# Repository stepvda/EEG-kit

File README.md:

# EEG Field Kit — Design & Production Package v2.4

**TI One Voice research programme** — [one.witysk.org](https://one.witysk.org), Brussels, Belgium
Board revision B · 2 September 2026

The complete manufacturing package for **EEG-CAR-01 Rev B**: a battery-powered, 16-channel EEG headset
built around an ESP32-S3 carrier board, together with the helmet and enclosure, the electrode harness,
the firmware, the production test programme and fixtures, and all the packing, quality and regulatory
documentation needed to produce the finished kit — flight case included.

The package is designed so that a manufacturer can quote, review and build from it directly: the
Gerbers, drill files, netlist, BOM and CPL files are included, along with every printed part, the
assembly work instructions and an end-to-end test programme that runs from Chrome over USB. For the
study itself — participants, collaborators, grant bodies and funders — see
[one.witysk.org/studies](https://one.witysk.org/studies).

---

## Status at a glance

**Nothing in this package has been manufactured or measured.** No board has been fabricated, no part
has been printed, no firmware has been flashed to silicon, and no electrode has touched a person.
Every performance figure is calculated, and each is labelled as calculated where it appears.

| Area | State |
|---|---|
| Carrier board routing | **Complete.** 145 of 145 nets connected, 0 DRC violations. **Released for review under RFQ-EEG-002A — not yet released for fabrication:** no human layout engineer has reviewed it, and 169 connections close at relaxed width or gap. |
| Firmware | **Built and boots under QEMU** (ESP-IDF v5.2.5, esp32s3). Never run on real hardware — no hardware exists. |
| Mechanical parts | 29 STL + 28 STEP released. Nothing has been printed. Foam case insert **not released for cutting** until the helmet shell is measured. |
| Test programme | Written and self-tested (57/57 interop checks). Never run against a physical unit. |
| Production simulation | 193 checks passed, 0 failed, 6 open items. |
| Safety | **Not done.** The safety review gates Phase 2; nothing goes on a head before it. |

**Read [`KNOWN_ISSUES.txt`](KNOWN_ISSUES.txt) before quoting or building anything.** It is the short
list, in one place, of what is wrong with the data as shipped — 6 open items and 22 unapproved
assumptions in 15 sections. Everything in it is also in the controlled documents; the file exists so
that problems are found here rather than at CAM time.

---

## Orientation — read in this order

1. **`README_package_index.txt` + `KNOWN_ISSUES.txt`** — the orientation pair. The index says what
   every folder is for and gives the rebuild commands (its header is stale at v2.2; this package
   is v2.4).
2. **`docs/RFQ-EEG-001 Rev E`** — the actual request: numbered requirements (E-, S-, F-, T-), the
   pricing template, and §9.4's correction-iteration terms for prototypes that arrive not working.
3. **`docs/DSN-EEG-003 Rev D`** — the governing document. Architecture, the carrier board, and the
   precedence rules that decide which document wins when two disagree.

**Precedence:** DSN-EEG-003 Rev D > RFQ-EEG-001 Rev E > ICD-EEG-006 > SCH-EEG-005 > DSN-EEG-002 >
PARTS-EEG-019 > RUL-EEG-021 > the bidder BOM. Where a number appears in a document *and* in
`tools/design.py`, **design.py governs** — `tools/emit_all.py` regenerates every fabrication file
from it in one pass, so the package cannot drift.

---

## Repository layout

| Path | Contents |
|---|---|
| `docs/` | 21 controlled documents (Rev-controlled, in `.md`, `.docx` and `.pdf`): the RFQ, the manufacturing design package, interface control, schematic set, assembly work instructions, harness wire list, test specification, fixture design, quality plan, risk & safety pack, regulatory file (incl. lithium shipping UN3481/PI967), service & refurbishment, participant card, packing & labelling, change control, approved vendor list, production simulation, part register, firmware build & provisioning, rulings register — plus the three workbooks: bidder BOM, internal costed BOM, manufacturer contacts. |
| `kicad/` | **EEG-CAR-01 Rev B fabrication pack:** routed `.kicad_pcb`, DRC report, BOM, two CPL files, fabrication/assembly/copper drawings, PCB spec sheet, machine-readable net report — and `gerber/`: 11 Gerber X2 layers, two Excellon drills, IPC-D-356A netlist, zipped, with a SHA-256 for every file. |
| `kicad/wh-bus-01/` | The second, tiny PCB: 14 × 10 × 0.8 mm bus board that splits the harness LED_V into eight contact-light tails. The helmet doesn't work without it. |
| `schematic/` | SCH-EEG-005 Rev B, an 8-sheet A3 schematic set (PDF + PNGs), generated from `tools/design.py`. Drawings only — there is no editable `.kicad_sch`. |
| `mech/` | Every printed and cut part: `stl/` (29 printable meshes), `step/` (28 parametric solids for dimensioning and inspection), `drawings/` (25 dimensioned sheets), `renders/` (25 shaded views), 7 foam-layer DXFs for the flight case, the hardware schedule and the mechanical release status. |
| `firmware/` | The ESP-IDF project (main.c, drivers, provisioning opcodes) and `release/`: four flashable ESP32-S3 images (bootloader, partition table, OTA data, app) with a SHA-256 manifest and the exact `esptool` command — no toolchain needed to program a board. `firmware/tools/` is the end-of-line provisioning station: ATECC608B keying, serial & calibration writes, signed-stream verification. |
| `webtest/` | **TOOL-EEG-022**, the connectivity test: one self-contained 52 kB HTML file an assembler double-clicks in Chrome to prove browser–computer–USB–device connectivity (no measurement, no server, nothing to install). The interop harness compiles the real `main.c` against ESP-IDF stubs and drives it with the real host protocol module — 57/57 checks green. |
| `fixtures/` | The four production test fixtures of JIG-EEG-009 as buildable data: PCB outlines and netlists (deliberately no copper), printed-part geometry, and RP2040 controller firmware speaking the FIXPROTO v1 line protocol. Nothing here has been built. |
| `records/` | The machine-readable per-unit test record of TST-EEG-004 §12: a JSON Schema, a stdlib-only validator, and a worked example (all-DEFERRED). No unit has been built, so the schema has never met real output. |
| `graphics/` | Board plots (four copper layers, fabrication drawing, drill map, assembly views, 3D renders) and `labels/`: the packing and marking artwork of PKG-EEG-015 — unit label, kit ID plate, 9 foam bay tags, carton set, lithium mark, tamper seal, disinfection card (22 SVG + 11 PDF). |
| `tools/` | The generator: 42 Python modules, 19,072 lines, 27 entry points. `design.py` is the single source of truth for the board; `mech_gen.py` for the printed parts. Five re-runnable verification gates check connectivity, DRC, placement, cross-document consistency and the 15-station production dry run. Every figure in this package can be regenerated from source. |
| `project/` | Why the kit exists: the 3-page partner proposal, the 161-page experiment design v4.2, and the 11-page project plan with its schedule and workstreams (supplier costs are placeholders). |
| `reports/` | Working DRC reports, metrics and the placement checklist from the routing campaign. |
| `constraints/` | Net rules used by the router. |

---

## The board

**EEG-CAR-01 Rev B** — 150.0 × 130.0 mm, four layers (L1 signal, L2/L3 reference planes split
AGND_REF/DGND, L4 signal), 30 connectors, 211 reference designators, 156 nets.

- 3,745 track segments, 552 through vias, 0 duplicates
- 145 of 145 nets one connected copper island; **0 DRC violations**
- Smallest clearance 0.260 mm, narrowest conductor 0.200 mm, smallest plated hole 0.300 mm
- No digital net in the analogue zone; exactly one AGND_REF-to-DGND bridge and one
  HARN_SHIELD-to-DGND bridge

The layout was produced by the programme's own constraint-aware autorouter and verified by
measurement on the finished polygons — but it has **not** been reviewed by a human layout
engineer. The DRC report lists every one of the 169 relaxed connections so a reviewer can go
straight to the places that need attention.

## Firmware

ESP-IDF v5.2.5, target esp32s3, Phase 1 configuration (secure boot off). Four release images with
SHA-256 checksums, a 920-line `main.c` with 16 host commands and 13 provisioning opcodes, drivers
for the ES8388 codec, SDMMC, ATECC608B, MAX17048 gauge and the envelope onset detector.

| What has happened | What it proves | What it does not |
|---|---|---|
| It builds, clean at `-Wall -Werror=all` | The image links and fits | That any of it is right |
| It boots under QEMU (esp32s3) | Bootloader, partition table and `app_main()` behave as written | Any peripheral — QEMU has no PSRAM, SD, ES8388 or ADS1299 |
| It agrees with the browser tool (57/57) | Framing, CRC, opcodes, the S-01 interlock | Anything about ESP-IDF or hardware |

**It has never run on silicon, and no hardware exists.** The SPI timing, every ADS1299 register
value, USB enumeration and the whole analogue front end are assumptions no silicon has answered.
F-08 (block signing) is unimplemented; the ATECC608B config template is only 4 of 128 bytes
reviewed — that write is irreversible, so it gates on a real part.

## Testing & quality

- **TST-EEG-004 Rev C** — the per-unit test: 32 steps T00–T30, with a 5,033-line JSON Schema and a
  stdlib-only validator so any two vendors emit the same record file.
- **JIG-EEG-009 Rev C + `fixtures/`** — four test fixtures as buildable data, with RP2040
  controller firmware passing 154 host checks.
- **TOOL-EEG-022** — the browser connectivity test (`webtest/EEG-Connectivity-Test.html`) and the
  interop harness that keeps firmware and protocol from drifting apart.
- **SIM-EEG-018** — a production simulation that walks one unit through all fifteen stations,
  purchase order to refurbishment: **193 passed, 0 failed, 6 open**.
- **ECO-EEG-016** — the change register that owns the document namespace and explains why
  everything is the way it is.

## Rebuilding the package from source

```sh
python3 tools/run_build.py          # route, pour, check            (~20 min)
python3 tools/emit_all.py --cached  # Gerbers, drawings, schematic
python3 tools/emit_extras.py        # spec sheet, netreport, STEP, manifest
python3 tools/mech_gen.py           # STL and STEP for every printed part
python3 tools/mech_drawings.py      # dimensioned drawings and renders
python3 tools/emit_workbooks.py     # the three spreadsheets
python3 tools/simulate_production.py --report docs/SIM-EEG-018_....md
python3 tools/make_docs.py          # A4 .docx and .pdf of every document

python3 tools/check_consistency.py  # cross-document consistency gate
python3 webtest/build.py            # rebuild the single-file connectivity tester
node webtest/tests/*.mjs            # protocol tests
sh webtest/tests/interop/run.sh     # firmware-vs-protocol interop (57 checks)
```

## Production phases

1. **Phase 1** — 2 prototypes
2. **Phase 2** — 10 kits
3. **Phase 3** — 10 to 40 further kits (25 to 50 total)

## Sponsorship

This study is run by a non-profit and funded by donations and grants that have not yet all been
secured. Any part of the work treated as sponsorship — a discounted prototype build, parts at
cost, donated units — is welcome, in return for named credit in the published open-hardware design
files, acknowledgement in the resulting papers and on the platform, and the case study of an
instrument you built being used in a pre-registered study.

## Licence & contact

Hardware and documents: **CC BY-SA 4.0** · Firmware: **MIT**

**Third-party datasheets are excluded from both grants.** Manufacturer datasheets and other
third-party documents referenced by this package remain the property of their respective
manufacturers, are referenced or redistributed for reference only, and are **not** covered by
the CC BY-SA 4.0 licence above. See [`docs/datasheets/README_datasheets.md`](docs/datasheets/README_datasheets.md)
for the index and [`docs/datasheets/third_party/LICENCE_NOTE.md`](docs/datasheets/third_party/LICENCE_NOTE.md)
for the terms.

**Stephane van der Aa** — Founder, TI One Voice
[one.witysk.org](https://one.witysk.org) · stephane@stepvda.com · +32 493 70 16 01

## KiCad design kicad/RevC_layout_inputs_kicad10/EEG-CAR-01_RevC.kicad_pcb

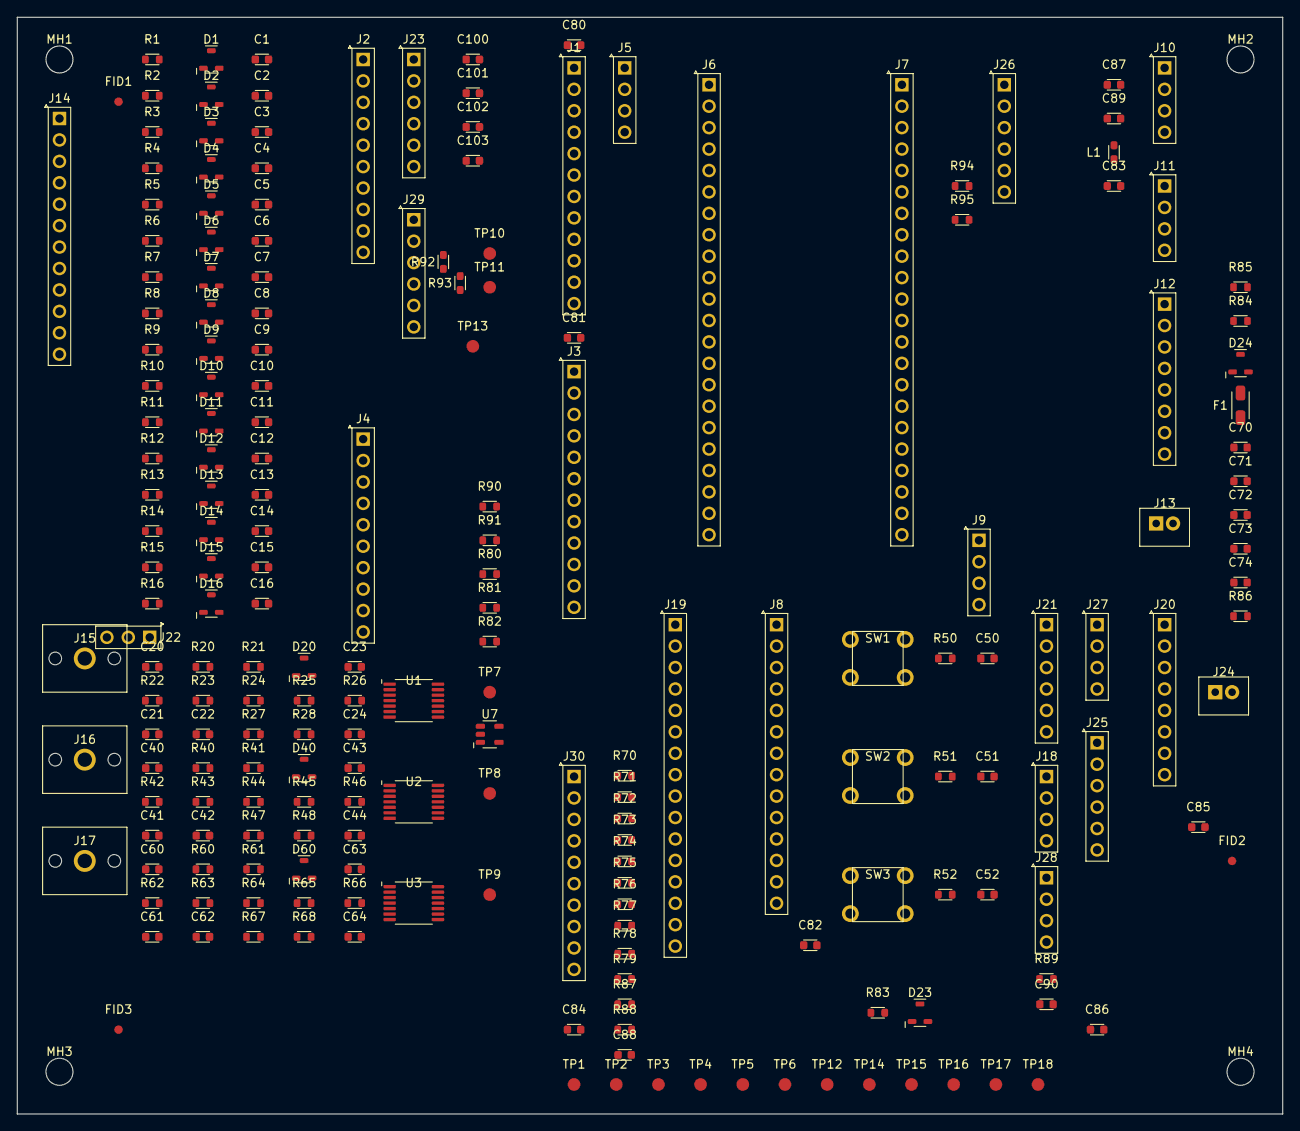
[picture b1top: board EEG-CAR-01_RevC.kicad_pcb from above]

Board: 4 copper layers, 150.0 x 130.0 mm, 211 parts (0 on the bottom side), 145 nets, no tracks yet.

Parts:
C1, C2, C3, C4, C5, C6, C7, C8, C9, C10, C11, C12, C13, C14, C15, C16, C21, C41, C61: 10n C0G 50V; C_0603_1608Metric
C20, C40, C60, C70, C71, C72, C73, C74, C89, C90, C100, C101: 10u X5R 16V; C_0603_1608Metric
C22, C42, C62: 22n C0G 50V; C_0603_1608Metric
C23, C24, C43, C44, C50, C51, C52, C63, C64, C80, C81, C82, C83, C84, C85, C86, C87, C88: 100n X7R 25V; C_0603_1608Metric
C102, C103: 100n X7R 50V; C_0603_1608Metric
D1, D2, D3, D4, D5, D6, D7, D8, D9, D10, D11, D12, D13, D14, D15, D16, D23: BAV99; SOT-23
D20, D40, D60: BAT54S; SOT-23
D24: PESD5V0S2BT; SOT-23
F1: PTC 1.1 A hold / 2.2 A trip; R_1206_3216Metric
FID1, FID2, FID3: global fiducial; Fiducial_1mm_Mask3mm
J1: ADS1299 module #1 digital; PinSocket_1x12_P2.54mm_Vertical
J2: ADS1299 module #1 analogue signals; PinSocket_1x10_P2.54mm_Vertical
J3: ADS1299 module #2 digital; PinSocket_1x12_P2.54mm_Vertical
J4: ADS1299 module #2 analogue signals; PinSocket_1x10_P2.54mm_Vertical
J5: ADS #1 DAISY_IN / CLKOUT stub; PinSocket_1x04_P2.54mm_Vertical
J6: ESP32-S3-DevKitC-1 row A; PinSocket_1x22_P2.54mm_Vertical
J7: ESP32-S3-DevKitC-1 row B; PinSocket_1x22_P2.54mm_Vertical
J8: ES8388 codec module; PinSocket_1x14_P2.54mm_Vertical
J9: Codec microphone feeds; PinSocket_1x04_P2.54mm_Vertical
J10: ADuM4160 USB isolator, device side; PinSocket_1x04_P2.54mm_Vertical
J11: ATECC608B breakout; PinSocket_1x04_P2.54mm_Vertical
J12: Charger + fuel gauge module; PinSocket_1x08_P2.54mm_Vertical
J13: 18650 protected cell; JST_PH_B2B-PH-K_1x02_P2.00mm_Vertical
J14: Helmet harness -- electrodes (12-way screened); PinSocket_1x12_P2.54mm_Vertical
J15: DIN 42802 EMG1 cheek; DIN42802_1p5mm_Socket
J16: DIN 42802 EMG2 submental; DIN42802_1p5mm_Socket
J17: DIN 42802 EMG3 laryngeal; DIN42802_1p5mm_Socket
J18: Boom microphone pigtail (TRRS); PinSocket_1x04_P2.54mm_Vertical
J19: 74HC595 contact-light driver; PinSocket_1x16_P2.54mm_Vertical
J20: microSD breakout, SDMMC 1-bit; PinSocket_1x08_P2.54mm_Vertical
J21: Boom-mic preamp module (part not settled, E-14); PinSocket_1x06_P2.54mm_Vertical
J22: EOG / spare electrode header; PinSocket_1x03_P2.54mm_Vertical
J23: ADS1299 module #1 analogue rails; PinSocket_1x06_P2.54mm_Vertical
J24: Charge input from the panel USB-C; JST_PH_B2B-PH-K_1x02_P2.00mm_Vertical
J25: Buck-boost module, TPS63020 class; PinSocket_1x06_P2.54mm_Vertical
J26: Debug / programming header; PinSocket_1x06_P2.54mm_Vertical
J27: Headphone jack pigtail; PinSocket_1x04_P2.54mm_Vertical
J28: Room microphone module; PinSocket_1x04_P2.54mm_Vertical
J29: ADS1299 module #2 analogue rails; PinSocket_1x06_P2.54mm_Vertical
J30: Helmet harness -- contact lights (10-way); PinSocket_1x10_P2.54mm_Vertical
L1: 600R at 100 MHz, 500 mA; L_0603_1608Metric
MH1, MH2, MH3, MH4: M3 x 3.2 mm NPTH; MountingHole_3.2mm_M3
R1, R2, R3, R4, R5, R6, R7, R8, R9, R10, R11, R12, R13, R14, R15, R16: 68k 0.1% 25ppm; R_0603_1608Metric
R20, R21, R23, R24, R40, R41, R43, R44, R60, R61, R63, R64: 10k 0.1%; R_0603_1608Metric
R22, R42, R62: 4k99 0.1%; R_0603_1608Metric
R25, R26, R45, R46, R65, R66: 215k 0.1%; R_0603_1608Metric
R27, R47, R67: 22k 0.1%; R_0603_1608Metric
R28, R48, R68: 2k2 0.1%; R_0603_1608Metric
R50, R51, R52, R81, R83, R88: 10k 1%; R_0603_1608Metric
R70, R71, R72, R73, R74, R75, R76, R77: 1k 1%; R_0603_1608Metric
R78, R79, R87, R90, R91, R92, R93: 0R; R_0603_1608Metric
R80: 470k 1%; R_0603_1608Metric
R82: 1M 1%; R_0603_1608Metric
R84, R86: 100k 1%; R_0603_1608Metric
R85: 150k 1%; R_0603_1608Metric
R89: 2k2 1% -- DNP; R_0603_1608Metric
R94, R95: 4k7 1%; R_0603_1608Metric
SW1: BTN_A response (green); SW_PUSH_6mm_H7.3mm
SW2: BTN_B response (blue); SW_PUSH_6mm_H7.3mm
SW3: BTN_STOP (red); SW_PUSH_6mm_H7.3mm
TP1: SCLK; TestPoint_Pad_D1.5mm
TP2: MOSI; TestPoint_Pad_D1.5mm
TP3: MISO; TestPoint_Pad_D1.5mm
TP4: DRDY; TestPoint_Pad_D1.5mm
TP5: I2S_BCLK; TestPoint_Pad_D1.5mm
TP6: I2S_LRCK; TestPoint_Pad_D1.5mm
TP7: ENV_STIM; TestPoint_Pad_D1.5mm
TP8: ENV_VOICE; TestPoint_Pad_D1.5mm
TP9: ENV_ROOM; TestPoint_Pad_D1.5mm
TP10: AVDD; TestPoint_Pad_D1.5mm
TP11: AVSS; TestPoint_Pad_D1.5mm
TP12: DVDD3V3; TestPoint_Pad_D1.5mm
TP13: AGND_REF; TestPoint_Pad_D1.5mm
TP14: DGND; TestPoint_Pad_D1.5mm
TP15: VSYS; TestPoint_Pad_D1.5mm
TP16: V5V; TestPoint_Pad_D1.5mm
TP17: NC_DRDY2; TestPoint_Pad_D1.5mm
TP18: CLK_ADS; TestPoint_Pad_D1.5mm
U1, U2, U3: OPA4376AIPW; TSSOP-14_4.4x5mm_P0.65mm
U7: TLV3201AIDBV; SOT-23-5

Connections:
AGND_REF: C1.2, C2.2, C3.2, C4.2, C5.2, C6.2, C7.2, C8.2, C9.2, C10.2, C11.2, C12.2, C13.2, C14.2, C15.2, C16.2, C21.2, C23.2, C24.2, C41.2, C43.2, C44.2, C61.2, C63.2, C64.2, C100.2, C101.2, C102.2, C103.2, J22.2, J23.4, J29.4, R28.2, R48.2, R68.2, R81.2, R90.1, TP13.1, U1.3, U1.5, U2.3, U2.5, U3.3, U3.5
AVDD: C23.1, C43.1, C63.1, C100.1, C102.1, D1.2, D2.2, D3.2, D4.2, D5.2, D6.2, D7.2, D8.2, D9.2, D10.2, D11.2, D12.2, D13.2, D14.2, D15.2, D16.2, J23.1, J23.5, R80.1, R92.2, TP10.1, U1.4, U2.4, U3.4, U7.5
AVDD2: J29.1, J29.5, R92.1
AVSS: C24.1, C44.1, C64.1, C101.1, C103.1, D1.1, D2.1, D3.1, D4.1, D5.1, D6.1, D7.1, D8.1, D9.1, D10.1, D11.1, D12.1, D13.1, D14.1, D15.1, D16.1, J23.2, J23.6, R93.2, TP11.1, U1.11, U2.11, U3.11, U7.2
AVSS2: J29.2, J29.6, R93.1
BIASIN: J23.3, J29.3
BIASOUT: C11.1, D11.3, J2.10, R11.2
BIAS_EL: J14.11, R11.1
BOOST_EN: J25.5, R86.2
BTN_A: C50.1, J6.4, R50.1, SW1.1
BTN_B: C51.1, J6.5, R51.1, SW2.1
BTN_STOP: C52.1, J6.6, R52.1, SW3.1
CHG_CE: J7.17, J12.4
CLK_ADS: J1.10, J3.10, J5.2, TP18.1
CMP_RAW: R82.1, R83.1, U7.1
CS: J1.7, J3.7, J6.16
DAISY: J3.5, J5.1
DGND: C50.2, C51.2, C52.2, C70.2, C71.2, C72.2, C73.2, C74.2, C80.2, C81.2, C82.2, C83.2, C84.2, C85.2, C86.2, C87.2, C88.2, C89.2, C90.2, D23.1, D24.2, D24.3, J1.2, J1.12, J3.2, J3.12, J5.3, J5.4, J6.22, J7.1, J7.21, J7.22, J8.2, J9.3, J10.4, J11.2, J12.2, J13.2, J18.2, J18.3, J18.4, J19.2, J20.2, J20.6, J20.7, J20.8, J21.2, J21.6, J24.2, J25.2, J25.4, J26.2, J28.2, R79.2, R85.2, R87.2, R90.2, R91.2, SW1.2, SW2.2, SW3.2, TP14.1
DRDY: J1.6, J6.20, TP4.1
DVDD3V3: C74.1, C80.1, C81.1, C82.1, C83.1, C84.1, C85.1, C86.1, C90.1, D23.2, J1.1, J3.1, J6.1, J6.2, J8.1, J11.1, J19.1, J20.1, J21.1, J26.1, J28.1, L1.1, R50.2, R51.2, R52.2, R88.2, R89.1, R94.2, R95.2, TP12.1
EMG1: C12.1, D12.3, J4.1, R12.2
EMG2: C13.1, D13.3, J4.2, R13.2
EMG3: C14.1, D14.3, J4.3, R14.2
EMGIN1: J15.1, R12.1
EMGIN2: J16.1, R13.1
EMGIN3: J17.1, R14.1
ENV1_ABS: R24.2, R25.1, U1.7
ENV1_AC: C20.2, R20.1, R23.1
ENV1_DIV: R27.2, R28.1, U1.12
ENV1_FLT: C22.2, R27.1, U1.8, U1.9
ENV1_HW: D20.1, R21.1, R22.1
ENV1_INM: D20.2, R20.2, R21.2, U1.2
ENV1_INP: C21.1, R26.2, U1.10
ENV1_MID: C22.1, R25.2, R26.1
ENV1_ROUT: D20.3, U1.1
ENV1_SUM: R22.2, R23.2, R24.1, U1.6
ENV2_ABS: R44.2, R45.1, U2.7
ENV2_AC: C40.2, R40.1, R43.1
ENV2_DIV: R47.2, R48.1, U2.12
ENV2_FLT: C42.2, R47.1, U2.8, U2.9
ENV2_HW: D40.1, R41.1, R42.1
ENV2_INM: D40.2, R40.2, R41.2, U2.2
ENV2_INP: C41.1, R46.2, U2.10
ENV2_MID: C42.1, R45.2, R46.1
ENV2_ROUT: D40.3, U2.1
ENV2_SUM: R42.2, R43.2, R44.1, U2.6
ENV3_ABS: R64.2, R65.1, U3.7
ENV3_AC: C60.2, R60.1, R63.1
ENV3_DIV: R67.2, R68.1, U3.12
ENV3_FLT: C62.2, R67.1, U3.8, U3.9
ENV3_HW: D60.1, R61.1, R62.1
ENV3_INM: D60.2, R60.2, R61.2, U3.2
ENV3_INP: C61.1, R66.2, U3.10
ENV3_MID: C62.1, R65.2, R66.1
ENV3_ROUT: D60.3, U3.1
ENV3_SUM: R62.2, R63.2, R64.1, U3.6
ENV_CMP: D23.3, J6.13, R83.2
ENV_ROOM: J4.6, TP9.1, U3.13, U3.14
ENV_STIM: J4.4, R82.2, TP7.1, U1.13, U1.14, U7.3
ENV_THR: R80.2, R81.1, U7.4
ENV_VOICE: J4.5, TP8.1, U2.13, U2.14
EOGIN1: J22.1, R15.1
EOGIN2: J22.3, R16.1
E_C3: J14.4, R4.1
E_C4: J14.5, R5.1
E_Cz: J14.2, R2.1
E_F7: J14.8, R8.1
E_Fz: J14.1, R1.1
E_Pz: J14.3, R3.1
E_T7: J14.6, R6.1
E_T8: J14.7, R7.1
HARN_SHIELD: J14.12, R91.1
HP_GND: J8.13, J27.3
HP_L: J8.11, J27.1
HP_R: J8.12, J27.2
HP_TAP: C20.1, J8.10
I2S_BCLK: J6.11, J8.4, TP5.1
I2S_DIN: J6.7, J8.6
I2S_DOUT: J6.15, J8.7
I2S_LRCK: J6.12, J8.5, TP6.1
I2S_MCLK: J6.10, J8.3
IN1: C1.1, D1.3, J2.1, R1.2
IN2: C2.1, D2.3, J2.2, R2.2
IN3: C3.1, D3.3, J2.3, R3.2
IN4: C4.1, D4.3, J2.4, R4.2
IN5: C5.1, D5.3, J2.5, R5.2
IN6: C6.1, D6.3, J2.6, R6.2
IN7: C7.1, D7.3, J2.7, R7.2
IN8: C8.1, D8.3, J2.8, R8.2
LED1: J30.1, R70.2
LED2: J30.2, R71.2
LED3: J30.3, R72.2
LED4: J30.4, R73.2
LED5: J30.5, R74.2
LED6: J30.6, R75.2
LED7: J30.7, R76.2
LED8: J30.8, R77.2
LED_GND: J30.10, R79.1
LED_MR: C88.1, J19.7, R88.1
LED_OE: J19.6, R87.1
LED_PWM: J7.16, R78.1
LED_SR_CLK: J7.6, J19.4
LED_SR_DATA: J7.7, J19.3
LED_SR_LATCH: J7.14, J19.5
LED_V: J30.9, R78.2
MIC_MUTE: J7.18, J9.4, J28.4
MISO: J1.5, J6.19, TP3.1
MOSI: J1.4, J3.4, J6.17, TP2.1
NC_DRDY2: J3.6, TP17.1
REF_L: J14.9, R9.1
REF_R: J14.10, R10.1
RESET: J1.9, J3.9, J6.9
RESET_EN: J6.3, J26.5
ROOM_PRE: C60.1, J9.2, J28.3
SCL: J7.5, J8.9, J11.4, J12.6, R95.1
SCLK: J1.3, J3.3, J6.18, TP1.1
SDA: J7.4, J8.8, J11.3, J12.5, R94.1
SD_CLK: J7.9, J20.3
SD_CMD: J7.10, J20.4
SD_D0: J7.8, J20.5
SPARE1: C15.1, D15.3, J4.7, R15.2
SPARE2: C16.1, D16.3, J4.8, R16.2
SRB1: C9.1, C10.1, D9.3, D10.3, J2.9, J4.9, R9.2, R10.2
SR_Q0: J19.8, R70.1
SR_Q1: J19.9, R71.1
SR_Q2: J19.10, R72.1
SR_Q3: J19.11, R73.1
SR_Q4: J19.12, R74.1
SR_Q5: J19.13, R75.1
SR_Q6: J19.14, R76.1
SR_Q7: J19.15, R77.1
START: J1.8, J3.8, J6.8
UART_RX: J7.3, J26.4
UART_TX: J7.2, J26.3
USB_DN: J7.20, J10.2
USB_DP: J7.19, J10.3
V5V: C72.1, C73.1, J1.11, J3.11, J6.21, J8.14, J25.3, TP16.1
VBAT: J12.1, J13.1
VBUS_CHG: D24.1, F1.2, J12.3, R84.1
VBUS_DET: J6.14, R84.2, R85.1
VBUS_IN: F1.1, J24.1
VDD_ISO: C87.1, C89.1, J10.1, L1.2
VOICE_PRE: C40.1, J9.1, J21.3
VOICE_RAW: J18.1, J21.4, R89.2
VSYS: C70.1, C71.1, J12.7, J25.1, R86.1, TP15.1

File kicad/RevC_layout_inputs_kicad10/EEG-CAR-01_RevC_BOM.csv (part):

Item,Qty,Designators,Value,Footprint,Manufacturer part number,Fit,Substitution,Notes
1,19,"C1 C2 C3 C4 C5 C6 C7 C8 C9 C10 C11 C12 C13 C14 C15 C16 C21 C41 C61","10n C0G 50V","C_0603_1608Metric","Murata GCM1885C1H103JA16D","fit","NOT SUBSTITUTABLE for C1 C2 C3 C4 C5 C6 C7 C8 C9 C10 C11 C12 C13 C14 C15 C16","RF filter to AGND_REF, Fz scalp"
2,12,"C20 C40 C60 C70 C71 C72 C73 C74 C89 C90 C100 C101","10u X5R 16V","C_0603_1608Metric","Murata GRM188R61C106MA73D","fit","equivalent permitted under AVL-EEG-017 section 6","input AC coupling into 10 kOhm: 1.6 Hz corner, envelope channel 1. ECO-EEG-027: 1 uF gave 15.9 Hz, which removes the envelope it is meant to pass."
3,3,"C22 C42 C62","22n C0G 50V","C_0603_1608Metric","Murata GCM1885C1H223JA16D","fit","equivalent permitted under AVL-EEG-017 section 6","Sallen-Key feedback C, sets Q = 0.74, channel 1.  C0G for the same reason as C21; the ratio 22/10 is what holds Q at 0.742."
4,18,"C23 C24 C43 C44 C50 C51 C52 C63 C64 C80 C81 C82 C83 C84 C85 C86 C87 C88","100n X7R 25V","C_0603_1608Metric","Murata GCM188R71E104KA57D","fit","equivalent permitted under AVL-EEG-017 section 6","AVDD decoupling at U1"
5,2,"C102 C103","100n X7R 50V","C_0603_1608Metric","Murata GCM188R71H104KA57D","fit","equivalent permitted under AVL-EEG-017 section 6","AVDD high-frequency decoupling"
6,17,"D1 D2 D3 D4 D5 D6 D7 D8 D9 D10 D11 D12 D13 D14 D15 D16 D23","BAV99","SOT-23","Nexperia BAV99,215","fit","NOT SUBSTITUTABLE for D1 D2 D3 D4 D5 D6 D7 D8 D9 D10 D11 D12 D13 D14 D15 D16","clamp to AVDD/AVSS, Fz scalp"
7,3,"D20 D40 D60","BAT54S","SOT-23","Nexperia BAT54S,215","fit","equivalent permitted under AVL-EEG-017 section 6","precision-rectifier Schottky pair (pin 3 at the op-amp output), channel 1"
8,1,"D24","PESD5V0S2BT","SOT-23","Nexperia PESD5V0S2BT,215","fit","equivalent permitted under AVL-EEG-017 section 6","transient suppressor on the charge input"
9,3,"FID1 FID2 FID3","global fiducial","Fiducial_1mm_Mask3mm","-","fabricated feature -- not purchased","equivalent permitted under AVL-EEG-017 section 6","1 mm copper, 3 mm mask opening, no net"
10,1,"F1","PTC 1.1 A hold / 2.2 A trip","R_1206_3216Metric","Bourns MF-MSMF110-2","fit","equivalent permitted under AVL-EEG-017 section 6","resettable fuse in the charge input"
11,1,"J1","ADS1299 module #1 digital","PinSocket_1x12_P2.54mm_Vertical","Samtec SSW-112-01-G-S or equivalent 2.54 mm socket strip","fit","equivalent permitted under AVL-EEG-017 section 6","1x12 socket: SPI, control lines, shared clock, 3V3 and 5 V feed to module #1"
12,1,"J2","ADS1299 module #1 analogue signals","PinSocket_1x10_P2.54mm_Vertical","Samtec SSW-110-01-G-S or equivalent 2.54 mm socket strip","fit","equivalent permitted under AVL-EEG-017 section 6","1x10 socket: eight EEG inputs, the SRB1 reference and the bias drive"
13,1,"J3","ADS1299 module #2 digital","PinSocket_1x12_P2.54mm_Vertical","Samtec SSW-112-01-G-S or equivalent 2.54 mm socket strip","fit","equivalent permitted under AVL-EEG-017 section 6","1x12 socket: SPI, control lines, shared clock, 3V3 and 5 V feed to module #2"
14,1,"J4","ADS1299 module #2 analogue signals","PinSocket_1x10_P2.54mm_Vertical","Samtec SSW-110-01-G-S or equivalent 2.54 mm socket strip","fit","equivalent permitted under AVL-EEG-017 section 6","1x10 socket: three EMG inputs, three envelope channels, two spares, SRB1"
15,1,"J5","ADS #1 DAISY_IN / CLKOUT stub","PinSocket_1x04_P2.54mm_Vertical","Samtec SSW-104-01-G-S or equivalent 2.54 mm socket strip","fit","equivalent permitted under AVL-EEG-017 section 6","1x4 stub: module #2 DOUT into module #1 DAISY_IN and the shared 2.048 MHz clock"
16,1,"J6","ESP32-S3-DevKitC-1 row A","PinSocket_1x22_P2.54mm_Vertical","Samtec SSW-122-01-G-S or equivalent 2.54 mm socket strip","fit","equivalent permitted under AVL-EEG-017 section 6","1x22 socket, DevKitC-1 left header. Row spacing to J7 is 22.86 mm (0.900 in)."
17,1,"J7","ESP32-S3-DevKitC-1 row B","PinSocket_1x22_P2.54mm_Vertical","Samtec SSW-122-01-G-S or equivalent 2.54 mm socket strip","fit","equivalent permitted under AVL-EEG-017 section 6","1x22 socket, DevKitC-1 right header"
18,1,"J8","ES8388 codec module","PinSocket_1x14_P2.54mm_Vertical","Samtec SSW-114-01-G-S or equivalent 2.54 mm socket strip","fit","equivalent permitted under AVL-EEG-017 section 6","1x14: I2S, I2C, headphone amplifier output, the stimulus envelope tap and 5 V"
19,1,"J9","Codec microphone feeds","PinSocket_1x04_P2.54mm_Vertical","Samtec SSW-104-01-G-S or equivalent 2.54 mm socket strip","fit","equivalent permitted under AVL-EEG-017 section 6","1x4: voice and room preamp outputs into the codec ADC, and the room-mic mute line"
20,1,"J10","ADuM4160 USB isolator, device side","PinSocket_1x04_P2.54mm_Vertical","Samtec SSW-104-01-G-S or equivalent 2.54 mm socket strip","fit","equivalent permitted under AVL-EEG-017 section 6","1x4: isolated USB D+/D-, isolated 3V3 and DGND. No carrier copper crosses the barrier. The module's host receptacle is USB-B on the qualified part, not USB-C; WH-09 adapts it. See RUL-EEG-021 section B."
21,1,"J11","ATECC608B breakout","PinSocket_1x04_P2.54mm_Vertical","Samtec SSW-104-01-G-S or equivalent 2.54 mm socket strip","fit","equivalent permitted under AVL-EEG-017 section 6","1x4: secure element on the shared I2C bus"
22,1,"J12","Charger + fuel gauge module","PinSocket_1x08_P2.54mm_Vertical","Samtec SSW-108-01-G-S or equivalent 2.54 mm socket strip","fit","equivalent permitted under AVL-EEG-017 section 6","1x8: bq24074-class charger with power path, and the MAX17048 gauge on I2C"
23,1,"J13","18650 protected cell","JST_PH_B2B-PH-K_1x02_P2.00mm_Vertical","JST B2B-PH-K-S(LF)(SN)","fit","equivalent permitted under AVL-EEG-017 section 6","battery input from the keyed cell carrier"
24,1,"J14","Helmet harness -- electrodes (12-way screened)","PinSocket_1x12_P2.54mm_Vertical","Samtec SSW-112-01-G-S or equivalent 2.54 mm socket strip","fit","equivalent permitted under AVL-EEG-017 section 6","1x12 socket: eight scalp electrodes, two ear references, the bias lead and the cable screen.  Nothing digital enters this connector."
25,1,"J15","DIN 42802 EMG1 cheek","DIN42802_1p5mm_Socket","Staubli SLB1,5-F / LB-I1,5","fit","NOT SUBSTITUTABLE -- E-09, S-02: PATIENT-CONNECTED under IEC 60601-1. A touch-proof DIN 42802 socket approved in writing from a sample. No 'or equivalent'","touch-proof 1.5 mm safety socket, EMG1 cheek, colour-coded"
26,1,"J16","DIN 42802 EMG2 submental","DIN42802_1p5mm_Socket","Staubli SLB1,5-F / LB-I1,5","fit","NOT SUBSTITUTABLE -- E-09, S-02: PATIENT-CONNECTED under IEC 60601-1. A touch-proof DIN 42802 socket approved in writing from a sample. No 'or equivalent'","touch-proof 1.5 mm safety socket, EMG2 submental, colour-coded"
27,1,"J17","DIN 42802 EMG3 laryngeal","DIN42802_1p5mm_Socket","Staubli SLB1,5-F / LB-I1,5","fit","NOT SUBSTITUTABLE -- E-09, S-02: PATIENT-CONNECTED under IEC 60601-1. A touch-proof DIN 42802 socket approved in writing from a sample. No 'or equivalent'","touch-proof 1.5 mm safety socket, EMG3 laryngeal, colour-coded"
28,1,"J18","Boom microphone pigtail (TRRS)","PinSocket_1x04_P2.54mm_Vertical","Samtec SSW-104-01-G-S or equivalent 2.54 mm socket strip","fit","equivalent permitted under AVL-EEG-017 section 6","1x4: to the panel TRRS jack at the left temple"
29,1,"J19","74HC595 contact-light driver","PinSocket_1x16_P2.54mm_Vertical","Samtec SSW-116-01-G-S or equivalent 2.54 mm socket strip","fit","equivalent permitted under AVL-EEG-017 section 6","1x16: shift-register module. Q0..Q7 drive the eight helmet contact lights."
30,1,"J20","microSD breakout, SDMMC 1-bit","PinSocket_1x08_P2.54mm_Vertical","Samtec SSW-108-01-G-S or equivalent 2.54 mm socket strip","fit","equivalent permitted under AVL-EEG-017 section 6","1x8: microSD card breakout wired for one-bit SDMMC (70 kB/s needed, 2 MB/s available)"
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
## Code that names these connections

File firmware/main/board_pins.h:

/*
 * board_pins.h -- EEG-CAR-01 Rev B pin map for FW-EEG-001.
 *
 * GENERATED by package_v2.4/tools from design.py.  Do not edit by hand: edit design.py
 * and regenerate, so the firmware and the board can never disagree.
 *
 * ECO-EEG-009: the Rev A map used GPIO35, 36 and 37 for the contact-light shift
 * register.  Those three pins carry the octal PSRAM on the ESP32-S3-DevKitC-1-N16R8
 * and are NOT CONNECTED on this carrier.  GPIO45 is the VDD_SPI strapping pin and is
 * also left open.  microSD is one-bit SDMMC for the same reason.
 *
 * Licence: MIT (firmware).
 */
#ifndef BOARD_PINS_H
#define BOARD_PINS_H

#define BOARD_REV        "B"
#define BOARD_NAME       "EEG-CAR-01"

#define PIN_SR_LATCH     0    /* J7.14  net LED_SR_LATCH */
#define PIN_I2C_SDA      1    /* J7.4   net SDA */
#define PIN_I2C_SCL      2    /* J7.5   net SCL */
#define PIN_ENV_CMP      3    /* J6.13  net ENV_CMP */
#define PIN_BTN_A        4    /* J6.4   net BTN_A */
#define PIN_BTN_B        5    /* J6.5   net BTN_B */
#define PIN_BTN_STOP     6    /* J6.6   net BTN_STOP */
#define PIN_I2S_DIN      7    /* J6.7   net I2S_DIN */
#define PIN_I2S_LRCK     8    /* J6.12  net I2S_LRCK */
#define PIN_I2S_DOUT     9    /* J6.15  net I2S_DOUT */
#define PIN_ADS_CS       10   /* J6.16  net CS */
#define PIN_ADS_MOSI     11   /* J6.17  net MOSI */
#define PIN_ADS_SCLK     12   /* J6.18  net SCLK */
#define PIN_ADS_MISO     13   /* J6.19  net MISO */
#define PIN_ADS_DRDY     14   /* J6.20  net DRDY */
#define PIN_ADS_START    15   /* J6.8   net START */
#define PIN_ADS_RESET    16   /* J6.9   net RESET */
#define PIN_I2S_MCLK     17   /* J6.10  net I2S_MCLK */
#define PIN_I2S_BCLK     18   /* J6.11  net I2S_BCLK */
#define PIN_USB_DN       19   /* J7.20  net USB_DN */
#define PIN_USB_DP       20   /* J7.19  net USB_DP */
#define PIN_MIC_MUTE     21   /* J7.18  net MIC_MUTE */
#define PIN_SD_CMD       38   /* J7.10  net SD_CMD */
#define PIN_SD_CLK       39   /* J7.9   net SD_CLK */
#define PIN_SD_D0        40   /* J7.8   net SD_D0 */
#define PIN_SR_DATA      41   /* J7.7   net LED_SR_DATA */
#define PIN_SR_CLK       42   /* J7.6   net LED_SR_CLK */
#define PIN_UART0_TX     43   /* J7.2   net UART_TX */
#define PIN_UART0_RX     44   /* J7.3   net UART_RX */
#define PIN_VBUS_DET     46   /* J6.14  net VBUS_DET */
#define PIN_CHG_CE       47   /* J7.17  net CHG_CE */
#define PIN_LED_V        48   /* J7.16  net LED_PWM */

/* Header positions that MUST remain unconnected on this hardware */
#define PIN_RESERVED_PSRAM_D5   35
#define PIN_RESERVED_PSRAM_D6   36
#define PIN_RESERVED_PSRAM_D7   37
#define PIN_RESERVED_VDD_SPI    45

/* Front end */
#define N_CH            16
#define N_DEV            2
#define ADS_GAIN_EEG    24
#define ADS_GAIN_EMG    12
#define ADS_GAIN_ENV     1

/* Contact lights: eight two-lead bicolour LEDs between LEDn and the LED_V common.
 * Phase A drives LED_V high and the wanted sites low  -> green.
 * Phase B drives LED_V low  and the wanted sites high -> red.
 * Alternating above 100 Hz shows amber.  At reset LED_V is an input, so nothing can
 * light whatever the shift register contains -- that is the dark-at-boot guarantee. */
#define N_LIGHTS         8
#define LIGHT_PHASE_HZ 240

#endif /* BOARD_PINS_H */

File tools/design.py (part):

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# ECO-EEG-028: J4 sat at y = 36 while the protection rows that feed its pins 1-3 and
# 7-8 sit at y = 52 to 70, so five electrode-class signals fanned 16 mm diagonally
# through the same window and sealed each other in (the Rev B route left EMG2, SPARE1
# and SPARE2 stranded at these pins).  At y = 50 the pins face their rows almost
# straight on: row 15 to pin 7 is now dead level.  SRB1 (pin 9) is reached around the
# south end of the socket; the envelope outputs enter pins 4-6 from the east.  What
# is uncertain: the SRB1 descent and the three envelope climbs now share the corridor
# east of the socket, which the router must arbitrate.
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# trunk taps.  Uncertain: pin 2 of J29 still has to reach pad 1 around the socket's
# own foreign pins, which is tight but no longer walled.
# Second refinement, same ECO: at (50.8, 31/35) the AVDD2 tree still dropped the
# whole J29 column from pin 1 to pin 5, and that drop walled pin 2 (AVSS2) in.  At
# the MID-LATITUDE of its two pins each link pulls both pins to itself directly --
# the minimum spanning tree prefers two short diagonals over the 10.2 mm column
# drop -- so no rail net runs the length of the socket any more.  R93 sits 2 mm
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# --- lower digital zone, in columns so every bundle has its own channel ----------------
# ECO-EEG-028: J9 sat at (66, 78), the far west of the digital zone, while every net
# on it terminates in the east -- J21 and J28 at x = 122, MIC_MUTE at J7.18 -- so three
# signals crossed the whole lower digital belt and pin 2 (ROOM_PRE) was sealed in by
# the shift-register feed bundle.  At (114, 62) it faces its partners across open
# board.  The ROOM_PRE and VOICE_PRE taps toward the envelope detectors still cross to
# the analogue zone; that is inherent in RFQ E-12/E-11, not in this placement.
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    add(f"R{70+i}", R06, "1k 1%", 72.0, 89.9 + i * 2.54, 0, "Vishay CRCW06031K00FKEA",
        f"contact-light series resistor, helmet site {i+1}", "D")
add("R78", R06, "0R", 72.0, 111.0, 0, "Vishay CRCW06030000Z0EA",
    "LED_V common drive link from GPIO48. 0R fitted; 47R is the approved alternate.", "D")
add("R79", R06, "0R", 72.0, 114.0, 0, "Vishay CRCW06030000Z0EA",
    "contact-light common return to DGND", "D")
add("R87", R06, "0R", 72.0, 117.0, 0, "Vishay CRCW06030000Z0EA",
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add("R88", R06, "10k 1%", 72.0, 120.0, 0, "Vishay CRCW060310K0FKEA",
    "74HC595 master-reset pull-up", "D")
add("C88", C06, "100n X7R 25V", 72.0, 123.0, 0, "Murata GCM188R71E104KA57D",
    "74HC595 power-on reset. Dark-at-boot is guaranteed by LED_V (GPIO48) floating.", "D")
add("J19", PS(16), "74HC595 contact-light driver", 78.0, 72.0, 0, SKT(16),
    "1x16: shift-register module. Q0..Q7 drive the eight helmet contact lights.", "D")
add("J8", PS(14), "ES8388 codec module", 90.0, 72.0, 0, SKT(14),
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    "1x6: VSYS to a regulated 5.0 V rail for the DevKit and both ADS1299 modules", "D")
# ECO-EEG-028: J26 sat at (128, 104), so UART0 ran 100 mm from the top of J7 down the
# board's most congested corner (the Rev B route shipped UART_TX and UART_RX with zero
# copper) and RESET_EN squeezed at minimum width.  Here, 12 mm east of J7 pins 2/3, in
# a block that carried almost no copper, all three are short runs; the move also
# vacates the x = 118-128 lane that HP_GND and ROOM_PRE need.  A bench cable still
# reaches it: the header is at the board's top-right, clear of the DevKit and 24 mm
# from the isolation strip.
add("J26", PS(6), "Debug / programming header", 117.0, 8.0, 0, SKT(6),
    "1x6: 3V3, GND, UART0 TX and RX, EN and NC_GPIO0 -- console and recovery flashing. "
    "Way 6 is the spare NC_GPIO0, not GPIO0: GPIO0 is committed to LED_SR_LATCH.", "D")
add("C86", C06, "100n X7R 25V", 128.0, 120.0, 0, "Murata GCM188R71E104KA57D",
    "local supply decoupling at J21", "D")
add("R83", R06, "10k 1%", 102.0, 118.0, 0, "Vishay CRCW060310K0FKEA",
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add("C89", C06, "10u X5R 16V", 130.0, 12.0, 0, "Murata GRM188R61C106MA73D",
    "isolator device-side bulk", "D")
# ECO-EEG-028: C80 sat at (70, 32) -- 26 mm from the J1.1 pin it decouples and exactly
# in the escape mouth of J1 pins 9-11, where its pads, its ground via and the DVDD3V3
# trunk that had to reach it walled RESET, CLK_ADS and V5V in (all three shipped
# stranded there in Rev B).  C81 did the same to J3 pins 9-11 from (70, 68).  Both now
# sit in line with the socket column, next to the pin 1 they serve; the DVDD3V3 trunk
# follows the west strip instead of crossing the SPI fan twice.
DEC3V3 = [("C80", "J1", 66.0, 3.3), ("C81", "J3", 66.0, 38.0),
          ("C83", "J11", 130.0, 20.0), ("C85", "J20", 140.0, 96.0),
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conn("J7", ["DGND", "UART_TX", "UART_RX", "SDA", "SCL", "LED_SR_CLK",
            "LED_SR_DATA", "SD_D0", "SD_CLK", "SD_CMD",
            "NC_GPIO37", "NC_GPIO36", "NC_GPIO35",
            "LED_SR_LATCH", "NC_GPIO45", "LED_PWM", "CHG_CE", "MIC_MUTE",
            "USB_DP", "USB_DN", "DGND", "DGND"])

conn("J8", ["DVDD3V3", "DGND", "I2S_MCLK", "I2S_BCLK", "I2S_LRCK", "I2S_DIN",
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conn("J12", ["VBAT", "DGND", "VBUS_CHG", "CHG_CE", "SDA", "SCL", "VSYS", "NC_CHG_STAT"])
conn("J24", ["VBUS_IN", "DGND"])
conn("J25", ["VSYS", "DGND", "V5V", "DGND", "BOOST_EN", "NC_BOOST_PG"])
conn("J26", ["DVDD3V3", "DGND", "UART_TX", "UART_RX", "RESET_EN", "NC_GPIO0"])
conn("J14", ["E_Fz", "E_Cz", "E_Pz", "E_C3", "E_C4", "E_T7", "E_T8", "E_F7",
             "REF_L", "REF_R", "BIAS_EL", "HARN_SHIELD"])
conn("J30", ["LED1", "LED2", "LED3", "LED4", "LED5", "LED6", "LED7", "LED8",
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
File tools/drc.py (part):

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
    # 10 star points
    ag = [t for t in tracks if t.net == "AGND_REF"]
    stats["AGND_REF / DGND bridges"] = 1        # by construction: R90 only
    stats["HARN_SHIELD / DGND bridges"] = 1     # R91 only

    # 11 via keep-outs
    for ref, clr in D.NO_VIA_ZONES:
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

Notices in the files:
kicad/RevC_layout_inputs_kicad10/EEG-CAR-01_RevC.kicad_pcb:
Generated from tools/design.py. Not edited by hand. Licence CC BY-SA 4.0.
